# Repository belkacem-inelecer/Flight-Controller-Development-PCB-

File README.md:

# Flight-Controller-Development-PCB-

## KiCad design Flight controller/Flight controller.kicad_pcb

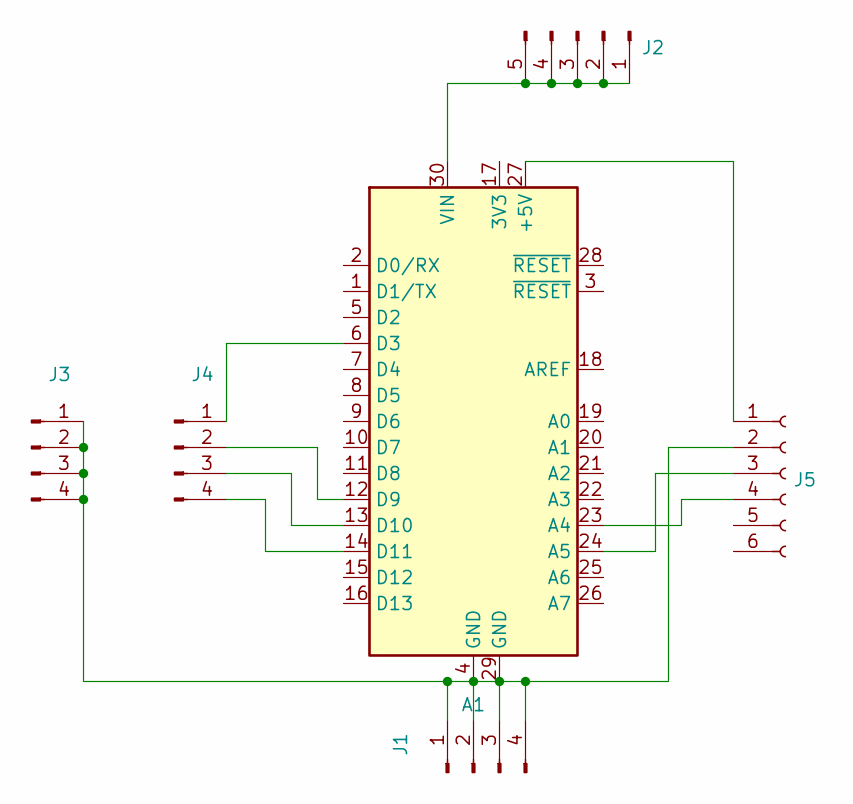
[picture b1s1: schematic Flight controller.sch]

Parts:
A1: Arduino_Nano_WithMountingHoles
J1, J3, J4: PinHeader_1x04_P1.00mm_Vertical
J2: PinHeader_1x05_P1.00mm_Vertical
J5: PinSocket_1x06_P1.00mm_Vertical

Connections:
unnamed: A1.6 (D3), J4.1
unnamed: A1.12 (D9), J4.2
unnamed: A1.13 (D10), J4.3
unnamed: A1.14 (D11), J4.4
unnamed: A1.23 (A4), J5.4
unnamed: A1.24 (A5), J5.3
unnamed: A1.27 (+5V), J5.1
unnamed: A1.4 (GND), A1.29 (GND), J1.1, J1.2, J1.3, J1.4, J3.1, J3.2, J3.3, J3.4, J5.2
unnamed: A1.30 (VIN), J2.1, J2.2, J2.3, J2.4, J2.5

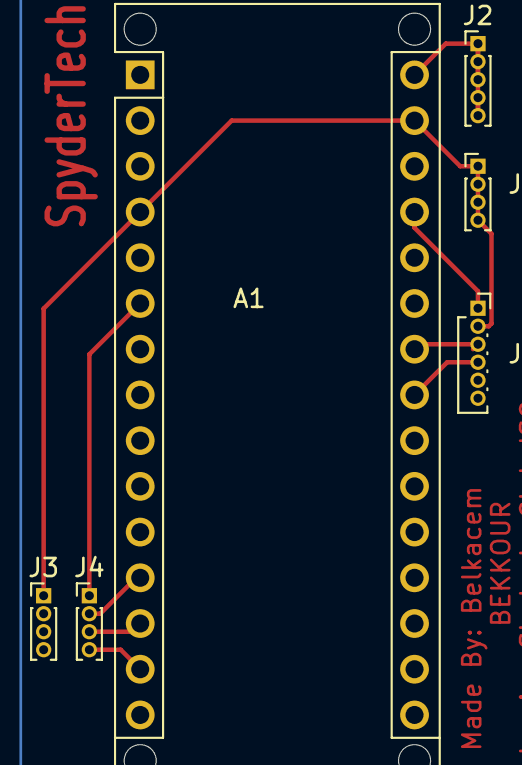
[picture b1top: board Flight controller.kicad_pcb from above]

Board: 2 copper layers, 6 parts (0 on the bottom side), 9 nets.
